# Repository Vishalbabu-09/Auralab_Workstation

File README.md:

# AURALAB WORKSTATION: Pocket-Sized Lab Bench & Hardware Diagnostic Toolkit

An advanced, ultra-portable multi-function test, measurement, and diagnostic platform engineered for the **KiCad PCB Design Contest**.

The **Auralab Workstation** packs a 12-bit digital oscilloscope, a variable bipolar $\pm15\text{V}$ bench power supply, an automated component curve tracer, and a smart hardware safety fault interrupter into a highly integrated, pocket-sized form factor.

---

## 1. System Working Modes & Operational Logic

The workstation utilizes the dual-core architecture of the **RP2040 microcontroller** to handle high-speed telemetry ingestion on one core while managing the graphical user interface (UI) and safety control loops on the second core.

### 📈 Mode 1: Oscilloscope Mode
* **What it does:** Captures, visualizes, and measures high-frequency external electrical signals in real time directly on the integrated 2.4" TFT display.
* **How it works:** Raw signals pass through an AC/DC coupling selector switch into a high-impedance **TL072 JFET operational amplifier** buffer circuit. This prevents the workstation from loading down the circuit under test. The conditioned signal is digitized by a dedicated **MCP3201 12-bit SAR ADC** operating over a high-speed SPI bus. Core 0 of the RP2040 processes the raw data arrays to compute signal parameters including **frequency, duty cycle, time period, $V_{pp}$ (peak-to-peak), and $V_{RMS}$**.

### ⚡ Mode 2: Bipolar DC Bench Power Supply Mode
* **What it does:** Acts as a precision-adjustable split-rail power supply delivering up to $\pm15\text{V}$ to drive external analog, op-amp, and prototype circuits via low-impedance screw terminals (`J2`).
* **How it works:** The user rotates the incremental digital encoder to set a target voltage. The RP2040 transmits this target via SPI to an **MCP42010 Dual Digital Potentiometer**. This digital pot dynamically alters the resistor feedback network of a high-efficiency **TPS65131 split-rail buck-boost regulator**, scaling the outputs symmetrically.

### 📊 Mode 3: Automated Component Curve Tracer Mode
* **What it does:** Plots the characteristic Voltage vs. Current ($V\text{-}I$) curves of un-biased two-terminal components (diodes, transistors, resistors, LEDs) directly onto the display to identify unknown parts or detect faulty silicon behavior.
* **How it works:** The workstation generates an internal hardware voltage sweep using a smoothed, high-frequency **Sweep PWM signal**. This low-pass filtered signal is amplified through a dedicated stage of the **TL072 op-amp**. As the voltage sweeps across the test terminal, an **INA219 high-side current monitor** reads the voltage drop across a $0.1\Omega$ shunt resistor, graphing the exact threshold voltages ($V_{th}$), saturation curves, and breakdown regions.

### 🛑 Mode 4: Smart Fault Detection & Overload Interrupter
* **What it does:** Acts as a real-time, hybrid hardware-software circuit breaker protecting both the workstation and your external device under test from short circuits, overcurrent conditions, and reverse polarity.
* **How it works:** The **INA219 current sensor** constantly monitors active current draw. If the current spikes past a safe user-defined ceiling, a hardware interrupt flag (`CURRENT_ALERT`) fires. The microcontroller instantly isolates the output terminals, flashes a high-intensity **ALERT_LED**, and triggers a resonant **Piezo Buzzer** to notify the user. Backup physical protection is maintained via an inline **Polyfuse (F1)** and steering clamping diodes.

---

## 2. Advanced 4-Layer PCB Stackup & Plane Allocation

To preserve 12-bit ADC accuracy while operating high-frequency digital clocks right next to high-gain analog buffers, this board utilizes a strict 4-layer mixed-signal stackup.

| Layer | Name | Copper Type | Main Signals & Plane Assignments |
| :--- | :--- | :--- | :--- |
| **Layer 1** | `F.Cu` (Top) | Signal / High-Speed | Component placement, SPI buses (Display, Flash, ADC), $\text{I}^2\text{C}$ lines, and sensitive analog trace lines. |
| **Layer 2** | `In1.Cu` | Split Ground Plane | **`GND` (Digital Ground Plane)** under the RP2040/Flash, and **`GNDA` (Analog Ground Plane)** under the Op-Amp/ADC/Reference. Isolated by a physical gap and joined strictly at a single point via a `NetTie_2` footprint near the power entrance. |
| **Layer 3** | `In2.Cu` | Dedicated Power Plane | Solid **`+3V3_DIGITAL`** power plane to provide clean, low-impedance power distribution across the digital logic core. |
| **Layer 4** | `B.Cu` (Bottom) | Signal Layer | Dedicated strictly to routing low-frequency control signals (Encoder pins, switch tracking lines) to keep them isolated from high-speed loops. |

---

## 3. Detailed Schematic & Hardware Architecture Breakdown

The hardware layout is organized into three highly optimized hierarchical sheets:

### 🔋 Module 1: Power Management & Filtration (Sheet 2)
Handles the regulation of raw input vectors, lithium-ion battery management, and high-current variable power rails.
* **USB-C Interface (`J3`):** Employs a 16-pin USB-C receptacle protected by an ultra-low capacitance **USBLC6-25C6 ESD array** to prevent electro-static damage across the differential lines.
* **BMS Stage (`U8`):** Uses a **TP4056 linear charger** with a precision $1.2\text{k}\Omega$ $R_{prog}$ resistor to regulate charging cycles safely for an attached Li-Po battery.
* **Split-Rail Engine (`U5`):** The **TPS65131 buck-boost converter** functions alongside high-current **SRR6048** power inductors ($L1, L2$) and high-speed Schottky catch diodes to cleanly establish the variable bipolar tracking rails.

### 🧠 Module 2: RP2040 Core & Interface Subsystem (Sheet 3)
Formulates the digital brain, memory maps, and human-machine interface routing.
* **Clocking Engine (`Y1`):** A low-jitter **12MHz Quartz Crystal** ensures ultra-stable operation for synchronous SPI data ingestion from the high-resolution ADC.
* **Storage Array (`U11`):** A **W25Q128JVS 128Mb QSPI Flash IC** stores custom GUI frames, display fonts, and analytical logging tables.

### 🔬 Module 3: Precision Analog Front-End (Sheet 4)
Handles conditioning, front-end buffering, clamping, and current telemetry tracking.
* **Precision Voltage Reference (`U3`):** Uses a low-drift **REF3033 bandgap voltage reference** to output a rock-solid, noise-free $3.3\text{V}$ absolute ceiling (`Vref_ADC`) directly to the SAR ADC, completely mitigating reference measurement drift.
* **Dynamic Range Shifter (`Q1`):** Features an automated hardware range shifter. By steering the gate of an **85170 N-Channel Power MOSFET**, the microcontroller alters the shunt resistor topology dynamically, switching scales between high-current tracking and micro-amp precision modes automatically.

---

## 4. Manufacturing & STEP Mechanical Export Validation

The project layout files have passed full Design Rule Checking (DRC) with 0 errors. A universal 3D mechanical master assembly model has been generated directly from the layout engine:

* **Export Format:** STEP (.step) standard mechanical vector.
* **Output Package Verified:** `Auralab_Workstation_Vishal.step` includes fully rendered 3D models for all high-profile custom footprints, including the 2.4" TFT module, the **XY126-3P** green terminal blocks, and the shielded **SRR6048** power inductors.
* **Compatibility:** Fully compliant with industry standard CAD software (SolidWorks, Autodesk Fusion 360, and free web viewers like `viewer.autodesk.com`).

---

## 5. Repository Directory Tree

```text
├── 3D Models Auralab_Workstation_Vishal/  <- Local STEP structural component cache
├── Auralab_Workstation Images/            <- Visual project logs and board renderings
├── Auralab_Workstation_Vishal schematic/  <- Schematic sheet files
├── Manufacturing/
│   ├── Drill/                             <- NC Drill files (.drl)
│   └── Gerbers/                           <- RS-274X Production plots (.gbr)
├── Auralab_Workstation_Vishal.kicad_pro   <- Master KiCad Project Hub File
├── Auralab_Workstation_Vishal.kicad_sch   <- Master Hierarchical Schematic Sheet
├── Auralab_Workstation_Vishal.kicad_pcb   <- Complete 4-Layer Routed PCB Layout
├── Auralab_Workstation_Vishal.pdf         <- Complete schematic printable export
└── LICENSE                                <- Open-source distribution documentation

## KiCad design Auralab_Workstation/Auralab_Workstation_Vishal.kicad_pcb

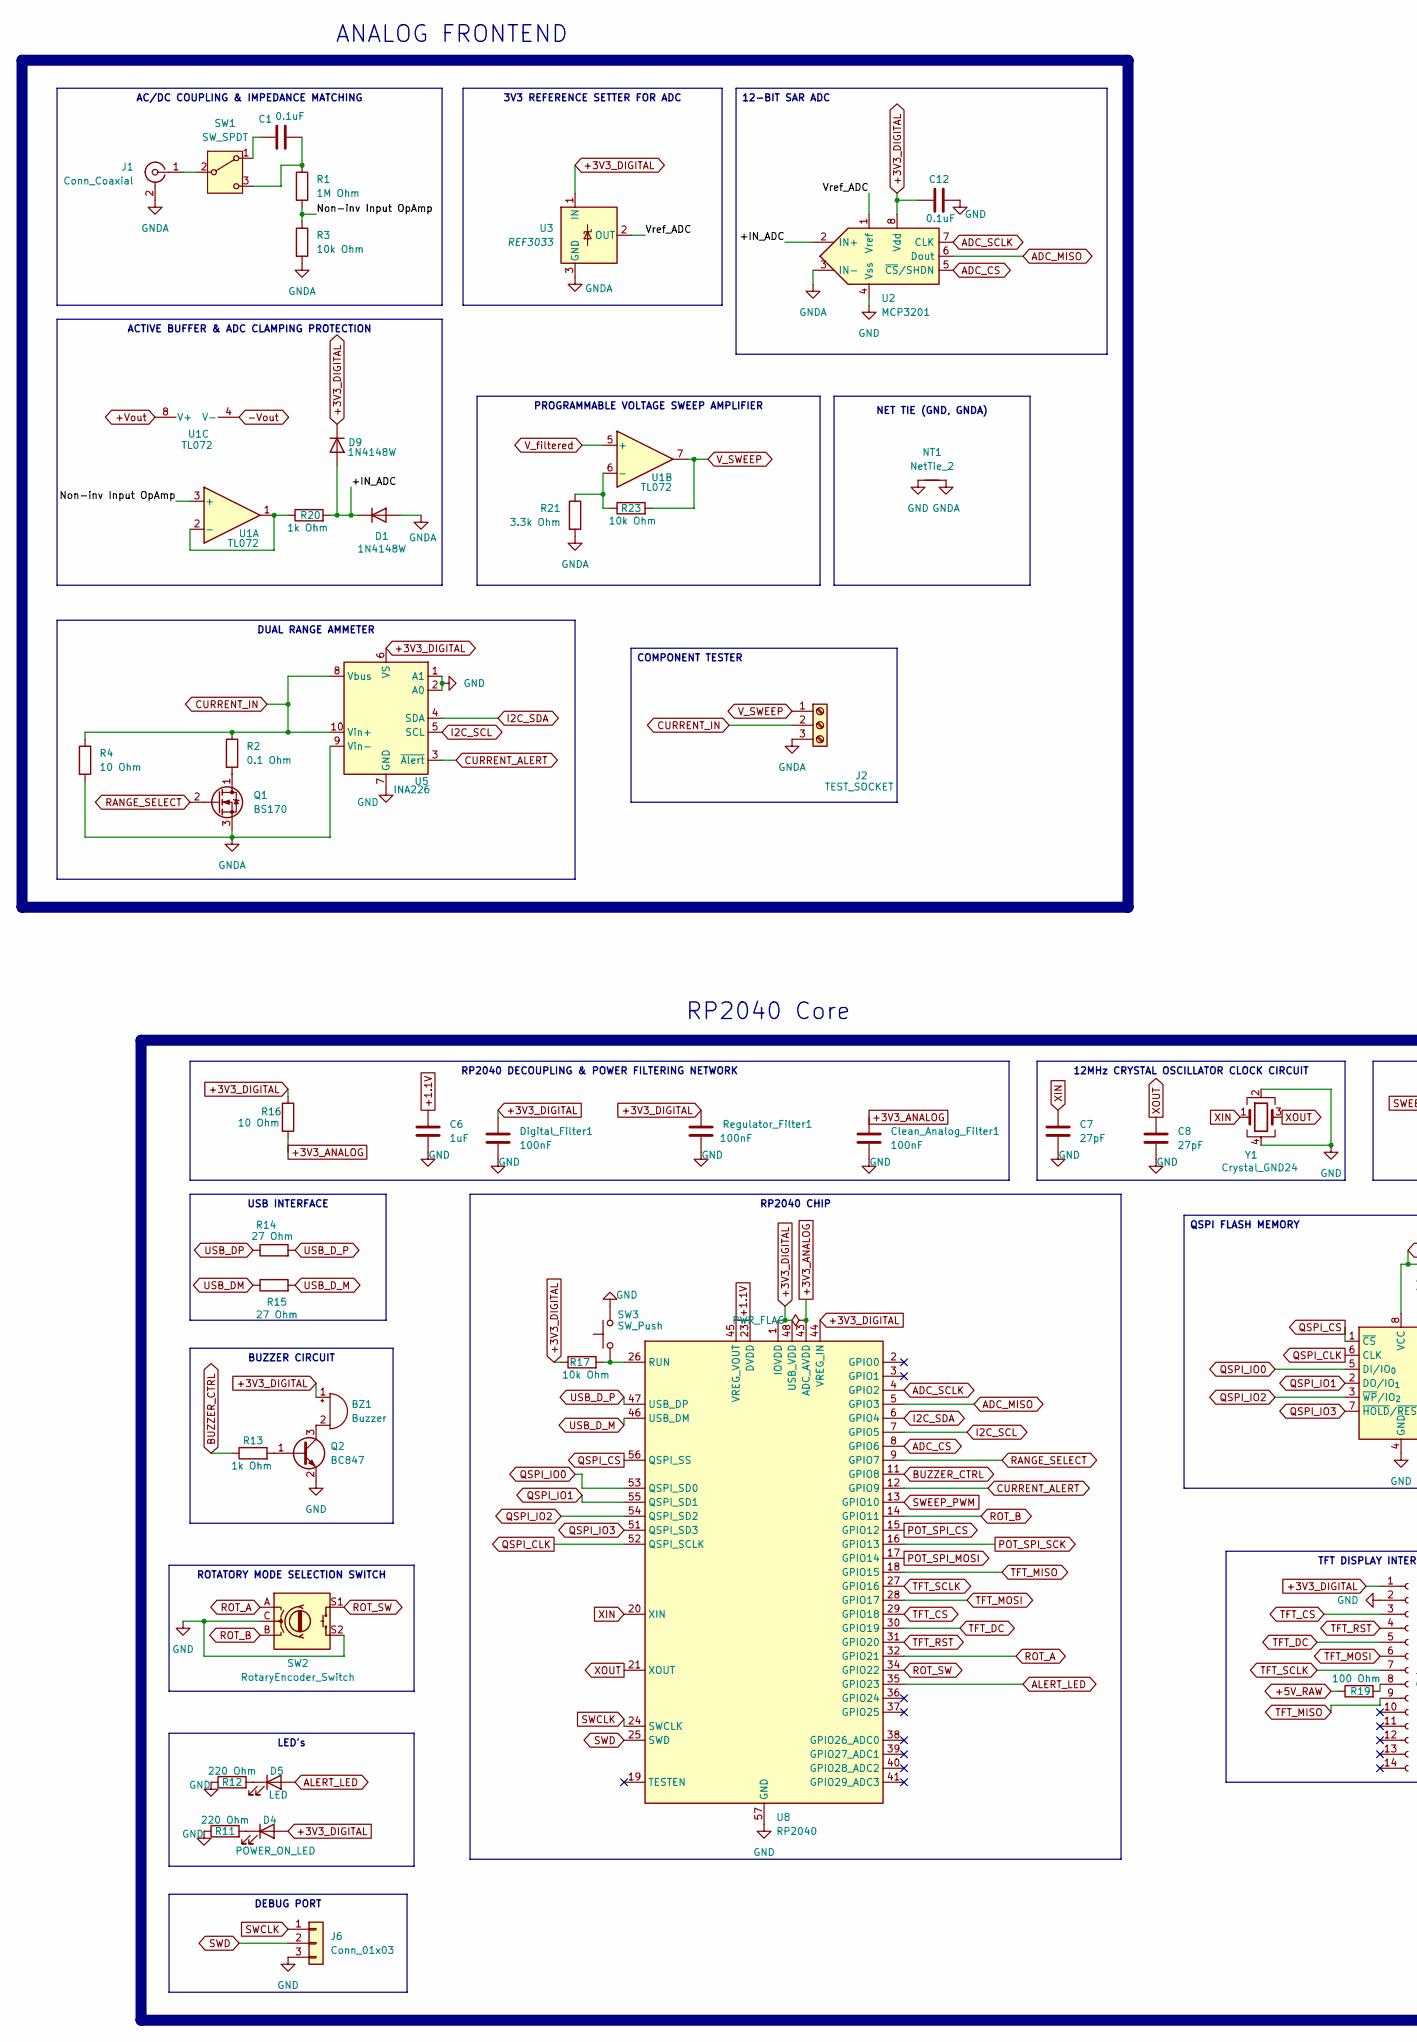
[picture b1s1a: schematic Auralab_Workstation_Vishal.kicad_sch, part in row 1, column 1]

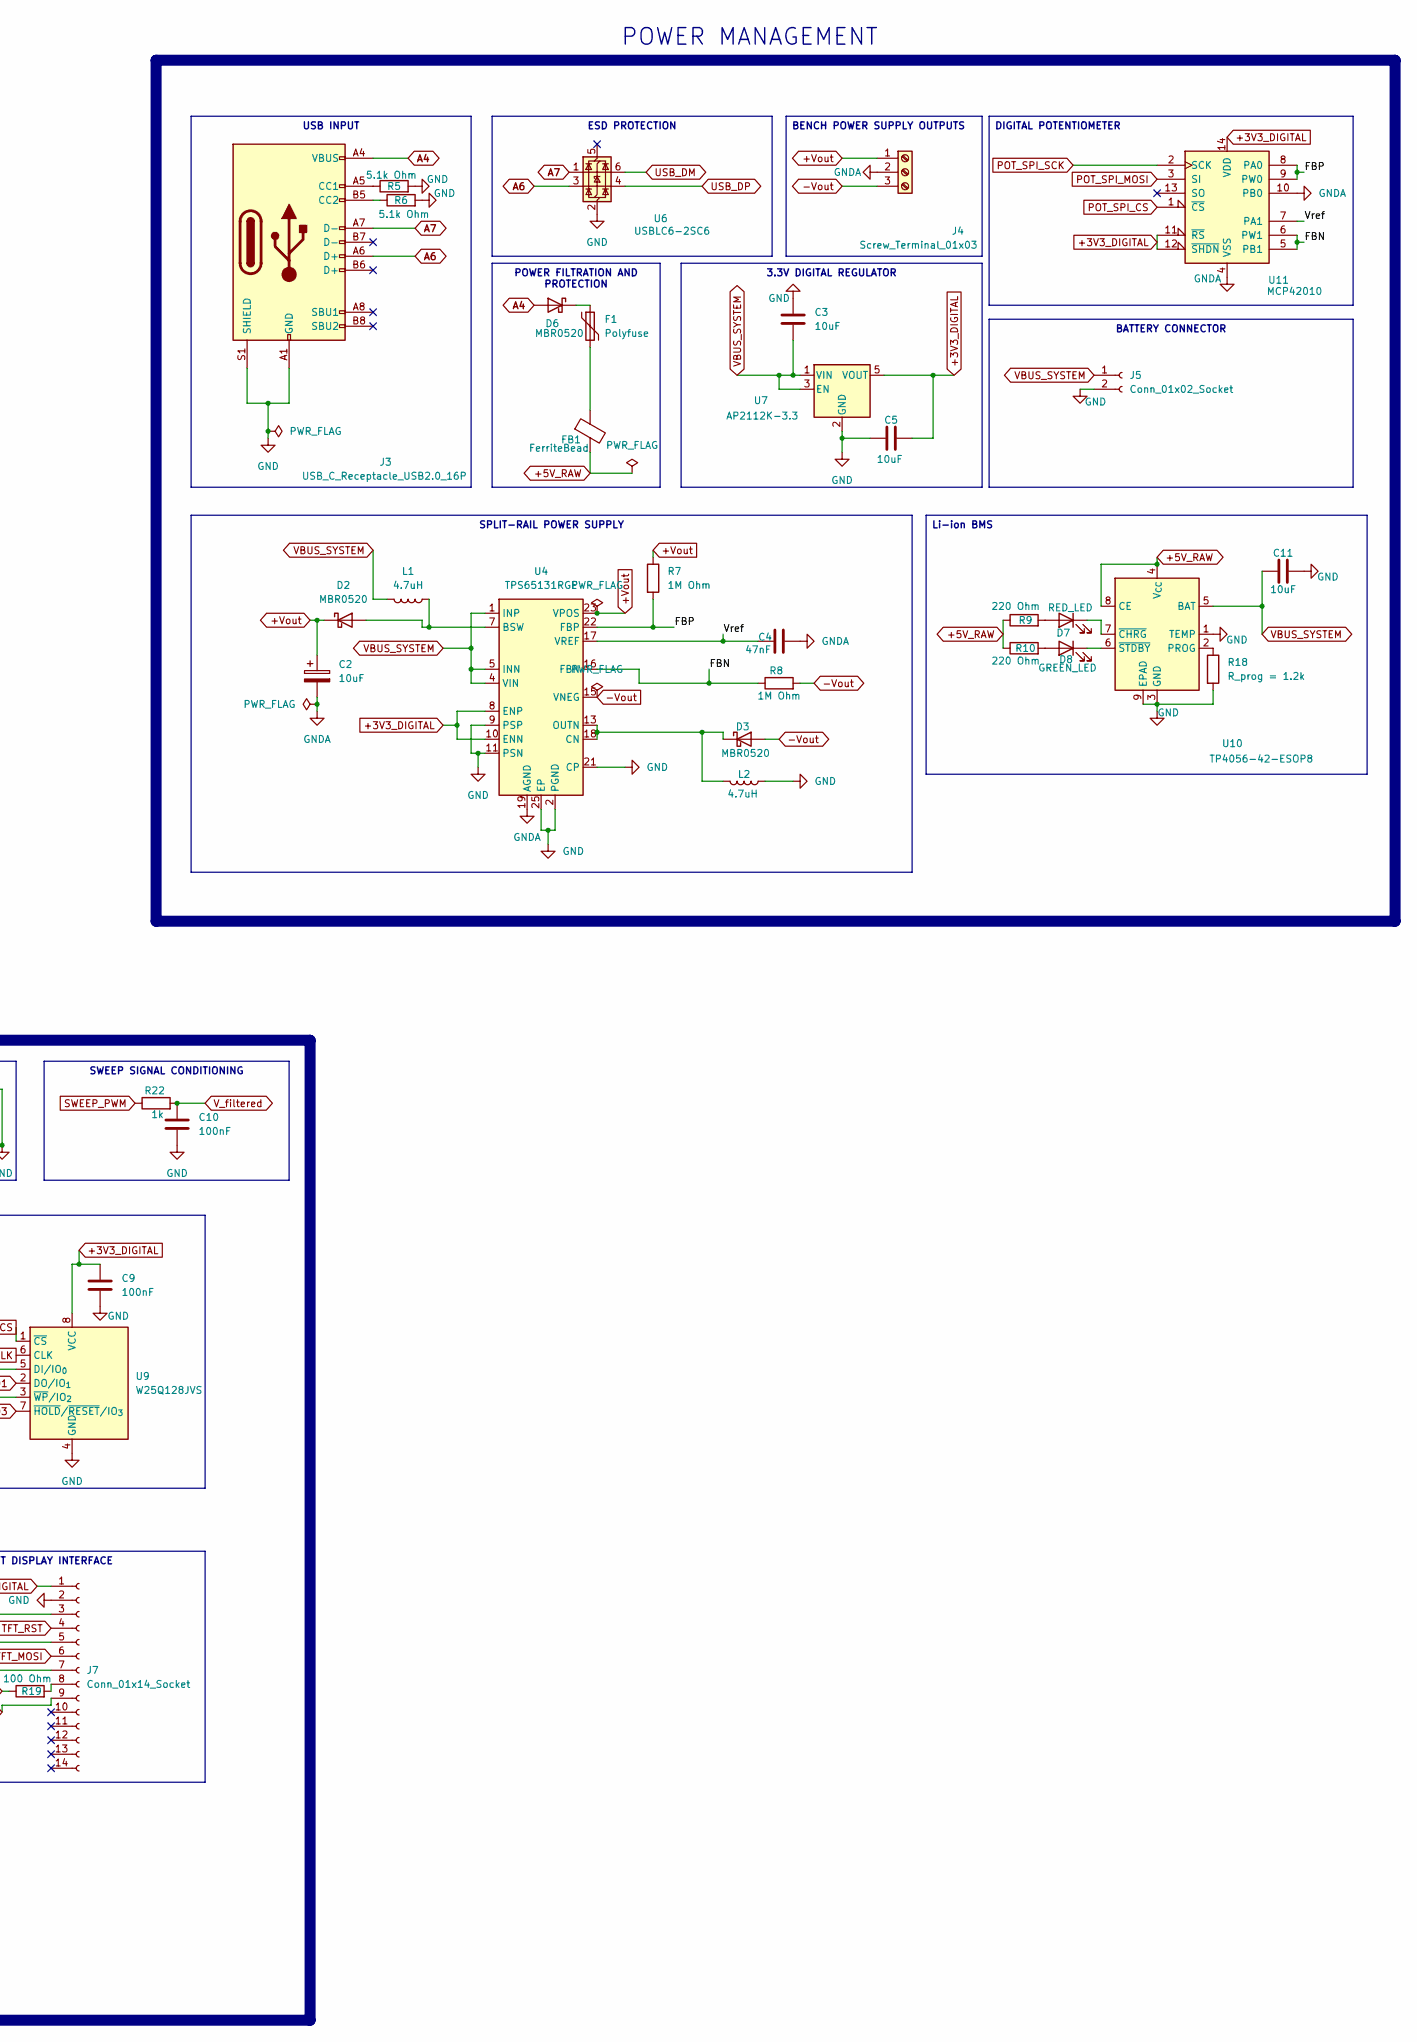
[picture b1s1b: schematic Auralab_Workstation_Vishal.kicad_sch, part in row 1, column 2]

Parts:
BZ1: Buzzer; Buzzer_CUI_CPT-9019S-SMT
C1, C12: 0.1uF; C_0805_2012Metric
C2: 10uF; CP_EIA-6032-28_Kemet-C_HandSolder
C3, C5, C11: 10uF; C_0805_2012Metric_Pad1.18x1.45mm_HandSolder
C4: 47nF; C_0805_2012Metric_Pad1.18x1.45mm_HandSolder
C6: 1uF; C_0805_2012Metric_Pad1.18x1.45mm_HandSolder
C7, C8: 27pF; C_0805_2012Metric_Pad1.18x1.45mm_HandSolder
C9, C10: 100nF; C_0805_2012Metric_Pad1.18x1.45mm_HandSolder
Clean_Analog_Filter1: 100nF; C_0805_2012Metric_Pad1.18x1.45mm_HandSolder
D1, D9: 1N4148W; D_SOD-123
D2, D3, D6: MBR0520; D_SOD-123
D4: POWER_ON_LED; LED_0805_2012Metric_Pad1.15x1.40mm_HandSolder
D5: LED; LED_0805_2012Metric_Pad1.15x1.40mm_HandSolder
D7: RED_LED; LED_0805_2012Metric_Pad1.15x1.40mm_HandSolder
D8: GREEN_LED; LED_0805_2012Metric_Pad1.15x1.40mm_HandSolder
Digital_Filter1: 100nF; C_0805_2012Metric_Pad1.18x1.45mm_HandSolder
F1: Polyfuse; Fuse_1206_3216Metric
FB1: FerriteBead; L_0805_2012Metric
J1: Conn_Coaxial; BNC_Amphenol_B6252HB-NPP3G-50_Horizontal
J2: TEST_SOCKET; TerminalBlock_Phoenix_MPT-0,5-3-2.54_1x03_P2.54mm_Horizontal
J3: USB_C_Receptacle_USB2.0_16P; USB_C_Receptacle_HCTL_HC-TYPE-C-16P-01A
J4: Screw_Terminal_01x03; TerminalBlock_MaiXu_MX126-5.0-03P_1x03_P5.00mm
J5: Conn_01x02_Socket; JST_PH_B2B-PH-K_1x02_P2.00mm_Vertical
J6: Conn_01x03; PinHeader_1x03_P2.54mm_Vertical
J7: Conn_01x14_Socket; PinSocket_1x14_P2.54mm_Vertical
L1, L2: 4.7uH; L_6.3x6.3_H3
NT1: NetTie_2
Q1: BS170; TO-92_Inline
Q2: BC847; SOT-23
R1: 1M Ohm; R_0805_2012Metric
R2: 0.1 Ohm; R_0805_2012Metric
R3, R23: 10k Ohm; R_0805_2012Metric
R4: 10 Ohm; R_0805_2012Metric
R5, R6: 5.1k Ohm; R_0805_2012Metric_Pad1.20x1.40mm_HandSolder
R7, R8: 1M Ohm; R_0805_2012Metric_Pad1.20x1.40mm_HandSolder
R9, R10, R11, R12: 220 Ohm; R_0805_2012Metric_Pad1.20x1.40mm_HandSolder
R13: 1k Ohm; R_0805_2012Metric_Pad1.20x1.40mm_HandSolder
R14, R15: 27 Ohm; R_0805_2012Metric_Pad1.20x1.40mm_HandSolder
R16: 10 Ohm; R_0805_2012Metric_Pad1.20x1.40mm_HandSolder
R17: 10k Ohm; R_0805_2012Metric_Pad1.20x1.40mm_HandSolder
R18: R_prog = 1.2k; R_0805_2012Metric_Pad1.20x1.40mm_HandSolder
R19: 100 Ohm; R_0805_2012Metric_Pad1.20x1.40mm_HandSolder
R20: 1k Ohm; R_0805_2012Metric
R21: 3.3k Ohm; R_0805_2012Metric
R22: 1k; R_0805_2012Metric_Pad1.20x1.40mm_HandSolder
Regulator_Filter1: 100nF; C_0805_2012Metric_Pad1.18x1.45mm_HandSolder
SW1: SW_SPDT; SW_SPDT_PCM12
SW2: RotaryEncoder_Switch; RotaryEncoder_Alps_EC11E-Switch_Vertical_H20mm
SW3: SW_Push; SW_PUSH-12mm_Wuerth-430476085716
U1: TL072; SOIC-8_3.9x4.9mm_P1.27mm
U2: MCP3201; SOIC-8_3.9x4.9mm_P1.27mm
U3: REF3033; SOT-23
U4: TPS65131RGE; VQFN-24-1EP_4x4mm_P0.5mm_EP2.45x2.45mm_ThermalVias
U5: INA226; MSOP-10_3x3mm_P0.5mm
U6: USBLC6-2SC6; SOT-23-6
U7: AP2112K-3.3; SOT-23-5
U8: RP2040; QFN-56-1EP_7x7mm_P0.4mm_EP3.2x3.2mm
U9: W25Q128JVS; SOIC-8_5.3x5.3mm_P1.27mm
U10: TP4056-42-ESOP8; SOIC-8-1EP_3.9x4.9mm_P1.27mm_EP2.41x3.3mm_ThermalVias
U11: MCP42010; SOIC-14_3.9x8.7mm_P1.27mm
Y1: Crystal_GND24; Crystal_SMD_3225-4Pin_3.2x2.5mm_HandSoldering

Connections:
+1.1V: C6.1, U8.23 (DVDD), U8.45 (VREG_VOUT), U8.50 (DVDD)
+3V3_ANALOG: Clean_Analog_Filter1.1, R16.2, U8.43 (ADC_AVDD); also elsewhere on the board
+3V3_DIGITAL: BZ1.1 (+), C5.1, C9.1, C12.1, D4.2 (A), D9.1 (K), Digital_Filter1.1, J7.1, R16.1, R17.1, Regulator_Filter1.1, U2.8 (Vdd), U3.1 (IN), U4.8 (ENP), U4.10 (ENN), U5.6 (VS), U7.5 (VOUT), U8.1 (IOVDD), U8.10 (IOVDD), U8.22 (IOVDD), U8.33 (IOVDD), U8.42 (IOVDD), U8.44 (VREG_IN), U8.48 (USB_VDD), U8.49 (IOVDD), U9.8 (VCC), U11.11 (~RS), U11.12 (~SHDN), U11.14 (VDD); also elsewhere on the board
+5V_RAW: FB1.2, R9.1, R10.1, R19.1, U10.4 (V_{CC}), U10.8 (CE)
+Vout: C2.1, D2.1 (K), J4.1, R7.1, U1.8 (V+), U4.23 (VPOS)
-Vout: D3.2 (A), J4.3, R8.2, U1.4 (V-), U4.15 (VNEG)
/+IN_ADC: D1.1 (K), D9.2 (A), R20.2, U2.2 (IN+)
/FBN: R8.1, U4.16 (FBN), U11.5 (PB1), U11.6 (PW1)
/FBP: R7.2, U4.22 (FBP), U11.8 (PA0), U11.9 (PW0)
/Non-inv Input OpAmp: R1.2, R3.1, U1.3 (+)
/Vref: C4.1, U4.17 (VREF), U11.7 (PA1)
/Vref_ADC: U2.1 (Vref), U3.2 (OUT)
A4: D6.2 (A), J3.A4 (VBUS), J3.A9 (VBUS), J3.B4 (VBUS), J3.B9 (VBUS)
A6: J3.A6 (D+), U6.3 (I/O2)
A7: J3.A7 (D-), U6.1 (I/O1)
ADC_CS: U2.5 (~CS/SHDN), U8.8 (GPIO6)
ADC_MISO: U2.6 (Dout), U8.5 (GPIO3)
ADC_SCLK: U2.7 (CLK), U8.4 (GPIO2)
ALERT_LED: D5.2 (A), U8.35 (GPIO23)
BUZZER_CTRL: R13.1, U8.11 (GPIO8)
CURRENT_ALERT: U5.3 (~Alert), U8.12 (GPIO9)
CURRENT_IN: J2.2, R2.1, R4.1, U5.8 (Vbus), U5.10 (Vin+)
GND: C3.1, C5.2, C6.2, C7.2, C8.2, C9.2, C10.2, C11.2, C12.2, Clean_Analog_Filter1.2, Digital_Filter1.2, J3.A1 (GND), J3.A12 (GND), J3.B1 (GND), J3.B12 (GND), J3.S1 (SHIELD), J3.SH, J5.2, J6.3, J7.2, L2.1, NT1.1, Q2.2 (E), R5.2, R6.2, R11.1, R12.1, R18.2, Regulator_Filter1.2, SW2.C, SW2.MP, SW2.S2, SW3.2, U2.4 (Vss), U4.2 (PGND), U4.3 (PGND), U4.9 (PSP), U4.11 (PSN), U4.21 (CP), U4.25 (EP), U5.1 (A1), U5.2 (A0), U5.7 (GND), U6.2 (GND), U7.2 (GND), U8.57 (GND), U9.4 (GND), U10.1 (TEMP), U10.3 (GND), U10.9 (EPAD), Y1.2, Y1.4; also elsewhere on the board
GNDA: C2.2, C4.2, D1.2 (A), J1.2 (Ext), J2.3, J4.2, NT1.2, Q1.3 (S), R3.2, R4.2, R21.2, U2.3 (IN-), U3.3 (GND), U4.19 (AGND), U5.9 (Vin-), U11.4 (VSS), U11.10 (PB0)
I2C_SCL: U5.5 (SCL), U8.7 (GPIO5)
I2C_SDA: U5.4 (SDA), U8.6 (GPIO4)
unnamed: BZ1.2 (-), Q2.3 (C)
unnamed: D2.2 (A), L1.1, U4.7 (BSW)
unnamed: D3.1 (K), L2.2, U4.13 (OUTN), U4.14 (OUTN), U4.18 (CN)
unnamed: D4.1 (K), R11.2
unnamed: D5.1 (K), R12.2
unnamed: D6.1 (K), F1.1
unnamed: D7.2 (A), R9.2
unnamed: D7.1 (K), U10.7 (~CHRG)
unnamed: D8.2 (A), R10.2
unnamed: D8.1 (K), U10.6 (~STDBY)
unnamed: F1.2, FB1.1
unnamed: J1.1 (In), SW1.2 (B)
unnamed: J3.A5 (CC1), R5.1
unnamed: J3.B5 (CC2), R6.1
unnamed: J7.8, R19.2
unnamed: Q1.1 (D), R2.2
unnamed: Q2.1 (B), R13.2
unnamed: C1.1, SW1.1 (A)
unnamed: C1.2, R1.1, SW1.3 (C)
unnamed: R20.1, U1.1, U1.2 (-)
unnamed: R21.1, R23.1, U1.6 (-)
unnamed: R17.2, SW3.1, U8.26 (RUN)
unnamed: R18.1, U10.2 (PROG)
POT_SPI_CS: U8.15 (GPIO12), U11.1 (~CS)
POT_SPI_MOSI: U8.17 (GPIO14), U11.3 (SI)
POT_SPI_SCK: U8.16 (GPIO13), U11.2 (SCK)
QSPI_CLK: U8.52 (QSPI_SCLK), U9.6 (CLK)
QSPI_CS: U8.56 (QSPI_SS), U9.1 (~CS)
QSPI_IO0: U8.53 (QSPI_SD0), U9.5 (DI/IO_{0})
QSPI_IO1: U8.55 (QSPI_SD1), U9.2 (DO/IO_{1})
QSPI_IO2: U8.54 (QSPI_SD2), U9.3 (~WP/IO_{2})
QSPI_IO3: U8.51 (QSPI_SD3), U9.7 (~HOLD/~RESET/IO_{3})
RANGE_SELECT: Q1.2 (G), U8.9 (GPIO7)
ROT_A: SW2.A, U8.32 (GPIO21)
ROT_B: SW2.B, U8.14 (GPIO11)
ROT_SW: SW2.S1, U8.34 (GPIO22)
SWCLK: J6.1, U8.24 (SWCLK)
SWD: J6.2, U8.25 (SWD)
SWEEP_PWM: R22.1, U8.13 (GPIO10)
TFT_CS: J7.3, U8.29 (GPIO18)
TFT_DC: J7.5, U8.30 (GPIO19)
TFT_MISO: J7.9, U8.18 (GPIO15)
TFT_MOSI: J7.6, U8.28 (GPIO17)
TFT_RST: J7.4, U8.31 (GPIO20)
TFT_SCLK: J7.7, U8.27 (GPIO16)
USB_DM: R15.1, U6.6 (I/O1)
USB_DP: R14.1, U6.4 (I/O2)
USB_D_M: R15.2, U8.46 (USB_DM)
USB_D_P: R14.2, U8.47 (USB_DP)
VBUS_SYSTEM: C3.2, C11.1, J5.1, L1.2, U4.1 (INP), U4.4 (VIN), U4.5 (INN), U4.6 (INN), U4.24 (INP), U7.1 (VIN), U7.3 (EN), U10.5 (BAT)
V_SWEEP: J2.1, R23.2, U1.7
V_filtered: C10.1, R22.2, U1.5 (+)
XIN: C7.1, U8.20 (XIN), Y1.1
XOUT: C8.1, U8.21 (XOUT), Y1.3

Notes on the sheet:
POWER MANAGEMENT
RP2040 Core
NET TIE (GND, GNDA)
ANALOG FRONTEND
3.3V DIGITAL REGULATOR
ROTATORY MODE SELECTION SWITCH
DEBUG PORT
3V3 REFERENCE SETTER FOR ADC
SPLIT-RAIL POWER SUPPLY
RP2040 DECOUPLING & POWER FILTERING NETWORK
COMPONENT TESTER
ESD PROTECTION
PROGRAMMABLE VOLTAGE SWEEP AMPLIFIER
SWEEP SIGNAL CONDITIONING
LED's
12MHz CRYSTAL OSCILLATOR CLOCK CIRCUIT
BUZZER CIRCUIT
Li-ion BMS
12-BIT SAR ADC
USB INPUT
ACTIVE BUFFER & ADC CLAMPING PROTECTION
USB INTERFACE
TFT DISPLAY INTERFACE
RP2040 CHIP
BENCH POWER SUPPLY OUTPUTS
POWER FILTRATION AND PROTECTION
BATTERY CONNECTOR
QSPI FLASH MEMORY
DIGITAL POTENTIOMETER
AC/DC COUPLING & IMPEDANCE MATCHING
DUAL RANGE AMMETER

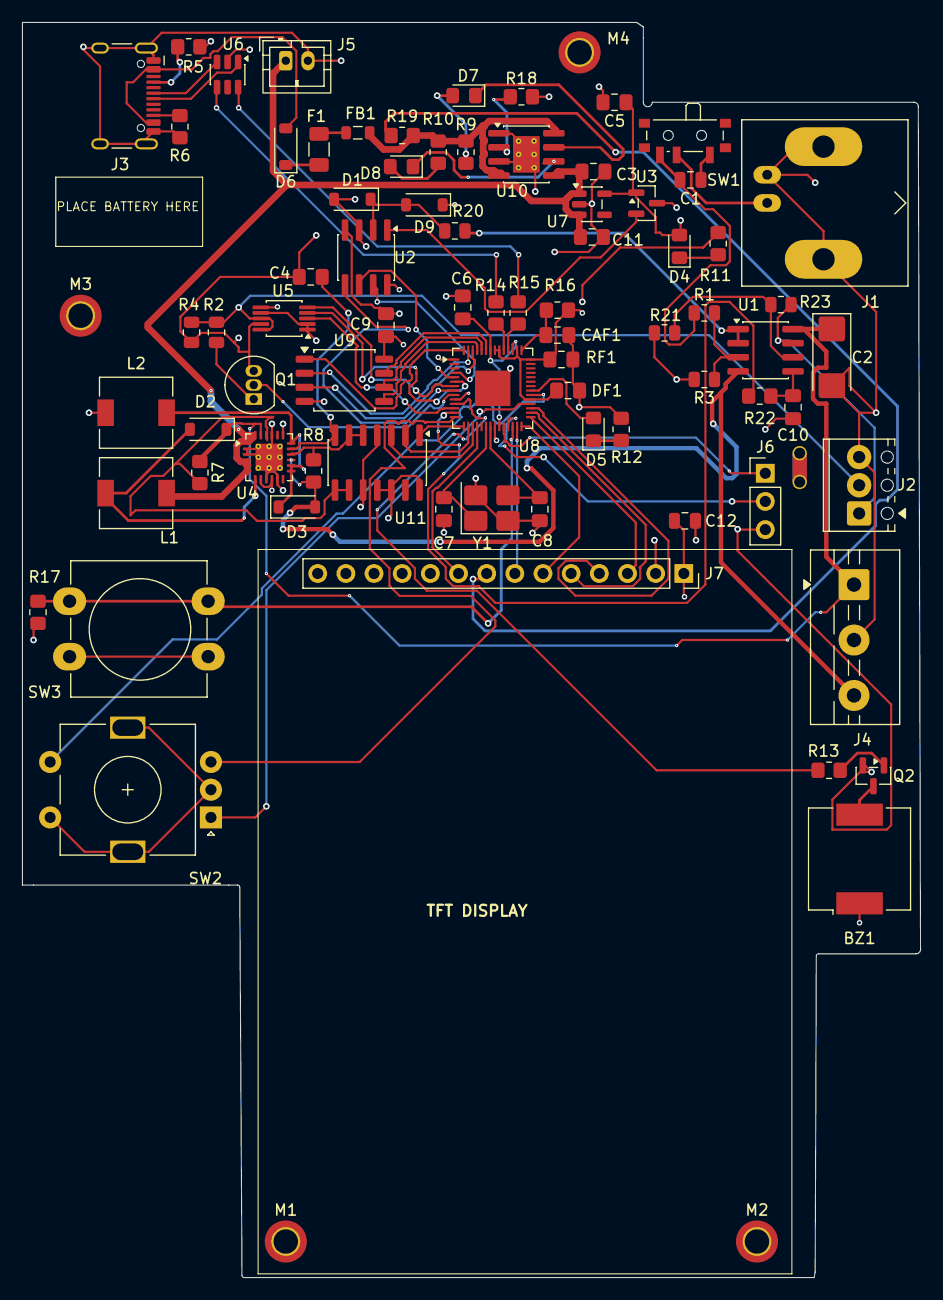
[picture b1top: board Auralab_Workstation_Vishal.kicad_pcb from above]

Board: 4 copper layers, 81.0 x 113.2 mm, 81 parts (0 on the bottom side), 80 nets.

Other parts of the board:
CAF1: 100nF; C_0805_2012Metric_Pad1.18x1.45mm_HandSolder
DF1: 100nF; C_0805_2012Metric_Pad1.18x1.45mm_HandSolder
M1, M2, M3, M4: MountingHole_2.2mm_M2_DIN965_Pad_TopBottom
RF1: 100nF; C_0805_2012Metric_Pad1.18x1.45mm_HandSolder

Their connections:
+3V3_ANALOG: CAF1.1; also elsewhere on the board
+3V3_DIGITAL: DF1.1, RF1.1; also elsewhere on the board
GND: CAF1.2, DF1.2, RF1.2; also elsewhere on the board

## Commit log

2026-06-05 Initial KiCad Architecture Layout
2026-06-06 started with connectionns
2026-06-06 just rotated one net label in ur sch
2026-06-06 oralavu panirken rp2040, nect un connections and mine sekanom that i will do tmrw
2026-06-07 I almost completed my part ig
2026-06-07 Made changes
2026-06-07 Now updated..
2026-06-07 Made few changes in IN2A66 in urs
2026-06-07 Updated few in ur sch
2026-06-08 Finished power management connections IG
2026-06-09 Deleted pcbway(1)
2026-06-11 Updated gnd, gnda in analog_frontend
2026-06-12 Updated footprints for rp2040
2026-06-12 Power kum footprints added
2026-06-12 Power management le few changes made inum full ah complete panle..
2026-06-13 Power management connections checked its perfect now
2026-06-14 Check analog part
2026-06-14 Check ERC
2026-06-14 ERC checked
2026-06-14 uPDATED AURALAB workstation
2026-06-14 see pdf
2026-06-14 working schematic
2026-06-14 pcb..
2026-06-15 Auralab_1 is updated copy
2026-06-15 see..
2026-06-15 Added MIT license
2026-06-16 removed unnecessary files
2026-06-16 Made few changes check
2026-06-16 renamed our old file as maincontest.kicadpcb
2026-06-19 Updated..
2026-06-19 Uploaded da..check
2026-06-19 Uploaded Gerber,Drill files
